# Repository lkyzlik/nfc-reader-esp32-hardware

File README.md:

# NFC Reader ESP32 Hardware
Hardware part of the secure NFC card reader developed on the ESP32 platform. My Bachelor thesis project created at Brno University of Technology.

## Other Parts
* Software part: [github.com/lkyzlik/nfc-reader-esp32-software](https://github.com/lkyzlik/nfc-reader-esp32-software)

## List of Components
| ID         | Component                   | Amount |
|------------|-----------------------------|--------|
| BT1        | LiPol battery 1200mAh       |      1 |
| C1, C3, C6 | Capacitor 100nF THT         |      3 |
| C2, C4     | Capacitor 10μF THT          |      2 |
| C5, C7     | Capacitor 100μF THT         |      2 |
| D1         | Shottky diode THT           |      1 |
| D2         | Red-green LED THT 5mm       |      1 |
| J1         | Barrel Jack                 |      1 |
| J2, J3     | Pin socket 1x15 (for ESP32) |      2 |
| J4         | Pin socket 1x8 (for PN532)  |      1 |
| Q1         | PMOS transistor SMD         |      1 |
| R1         | Resistor 2kΩ THT            |      1 |
| R2,R3      | Resistor 330Ω THT           |      2 |
| R4, R6, R7 | Resistor 4.7kΩ THT          |      3 |
| R5         | Resistor 1kΩ THT            |      1 |
| U1         | MCP73832 IC SMD             |      1 |
| U2         | LF33 IC SMD                 |      1 |
|            | Source DC 5V                |      1 |
|            | PCB with manufacturing      |      1 |
|            | [ESP32 DevKit v1](https://docs.zerynth.com/latest/official/board.zerynth.doit_esp32/docs/index.html)      |      1 |
|            | [PN532 module](https://components101.com/wireless/pn532-nfc-rfid-module)     |      1 |

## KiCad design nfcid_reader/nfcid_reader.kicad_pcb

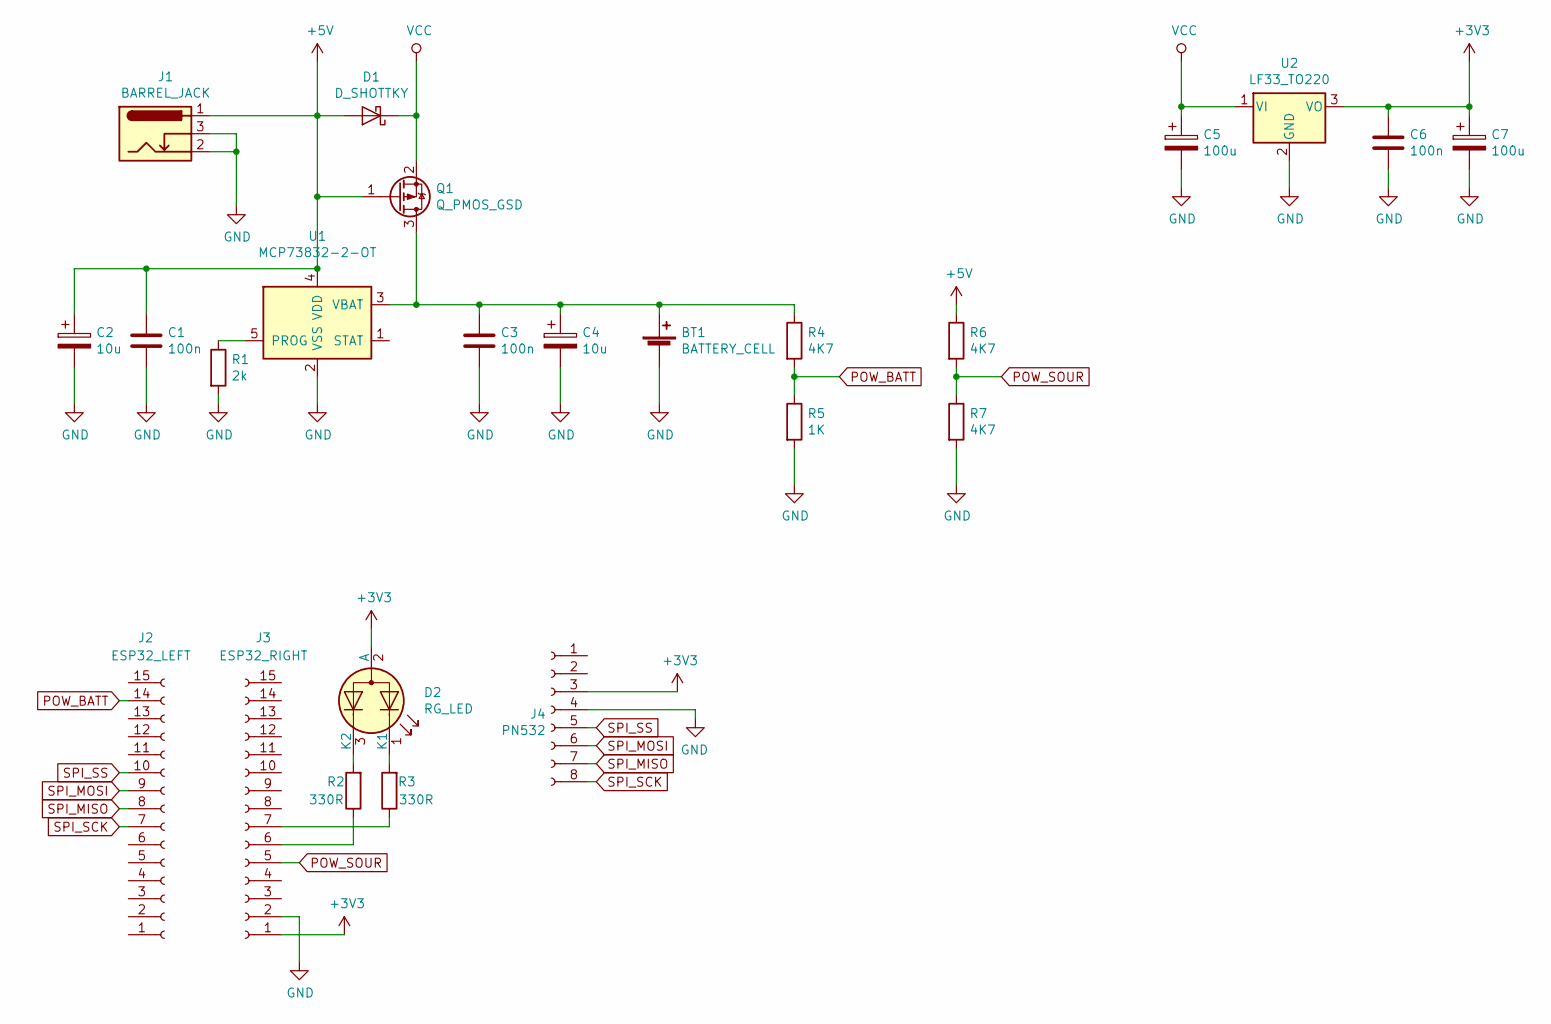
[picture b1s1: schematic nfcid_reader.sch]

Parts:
BT1: BATTERY_CELL; TestPoint_2Pads_Pitch2.54mm_Drill0.8mm
C1, C3, C6: 100n; C_Disc_D3.0mm_W1.6mm_P2.50mm
C2, C4: 10u; CP_Radial_D6.3mm_P2.50mm
C5, C7: 100u; CP_Radial_D6.3mm_P2.50mm
D1: D_SHOTTKY; D_A-405_P7.62mm_Horizontal
D2: RG_LED; LED_D5.0mm-3
J1: BARREL_JACK; BarrelJack_Horizontal
J2: ESP32_LEFT; PinSocket_1x15_P2.54mm_Vertical
J3: ESP32_RIGHT; PinSocket_1x15_P2.54mm_Vertical
J4: PN532; PinSocket_1x08_P2.54mm_Horizontal
Q1: Q_PMOS_GSD; SOT-23_Handsoldering
R1: 2k; R_Axial_DIN0204_L3.6mm_D1.6mm_P7.62mm_Horizontal
R2, R3: 330R; R_Axial_DIN0204_L3.6mm_D1.6mm_P7.62mm_Horizontal
R4, R6, R7: 4K7; R_Axial_DIN0204_L3.6mm_D1.6mm_P7.62mm_Horizontal
R5: 1K; R_Axial_DIN0204_L3.6mm_D1.6mm_P7.62mm_Horizontal
U1: MCP73832-2-OT; SOT-23-5
U2: LF33_TO220; TO-252-2

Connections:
+3V3: C6.1, C7.1, D2.2 (A), J3.1, J4.3, U2.3 (VO)
+5V: C1.1, C2.1, D1.2 (A), J1.1, Q1.1 (G), R6.1, U1.4 (VDD)
GND: BT1.2 (-), C1.2, C2.2, C3.2, C4.2, C5.2, C6.2, C7.2, J1.2, J1.3, J3.2, J4.4, R1.2, R5.2, R7.2, U1.2 (VSS), U2.2 (GND)
unnamed: BT1.1 (+), C3.1, C4.1, Q1.3 (D), R4.1, U1.3 (VBAT)
unnamed: D2.1 (K1), R3.2
unnamed: D2.3 (K2), R2.2
unnamed: J3.6, R2.1
unnamed: J3.7, R3.1
unnamed: R1.1, U1.5 (PROG)
POW_BATT: J2.14, R4.2, R5.1
POW_SOUR: J3.5, R6.2, R7.1
SPI_MISO: J2.8, J4.7
SPI_MOSI: J2.9, J4.6
SPI_SCK: J2.7, J4.8
SPI_SS: J2.10, J4.5
VCC: C5.1, D1.1 (K), Q1.2 (S), U2.1 (VI)

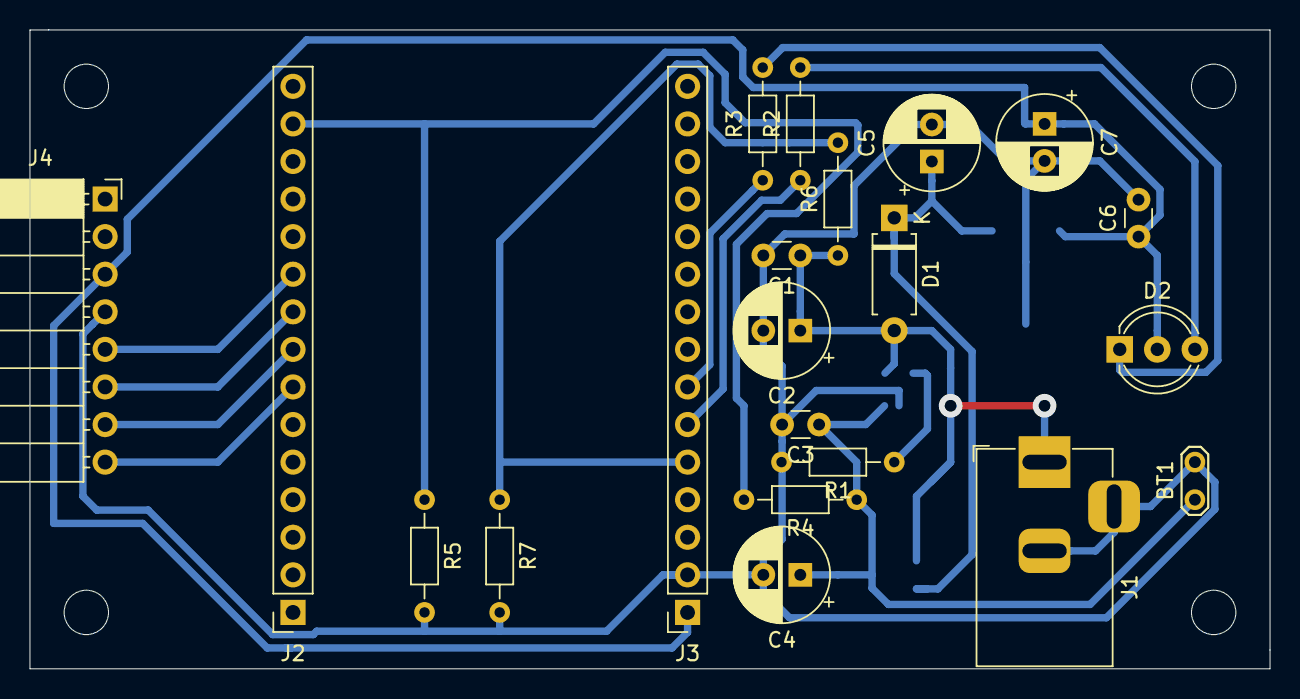
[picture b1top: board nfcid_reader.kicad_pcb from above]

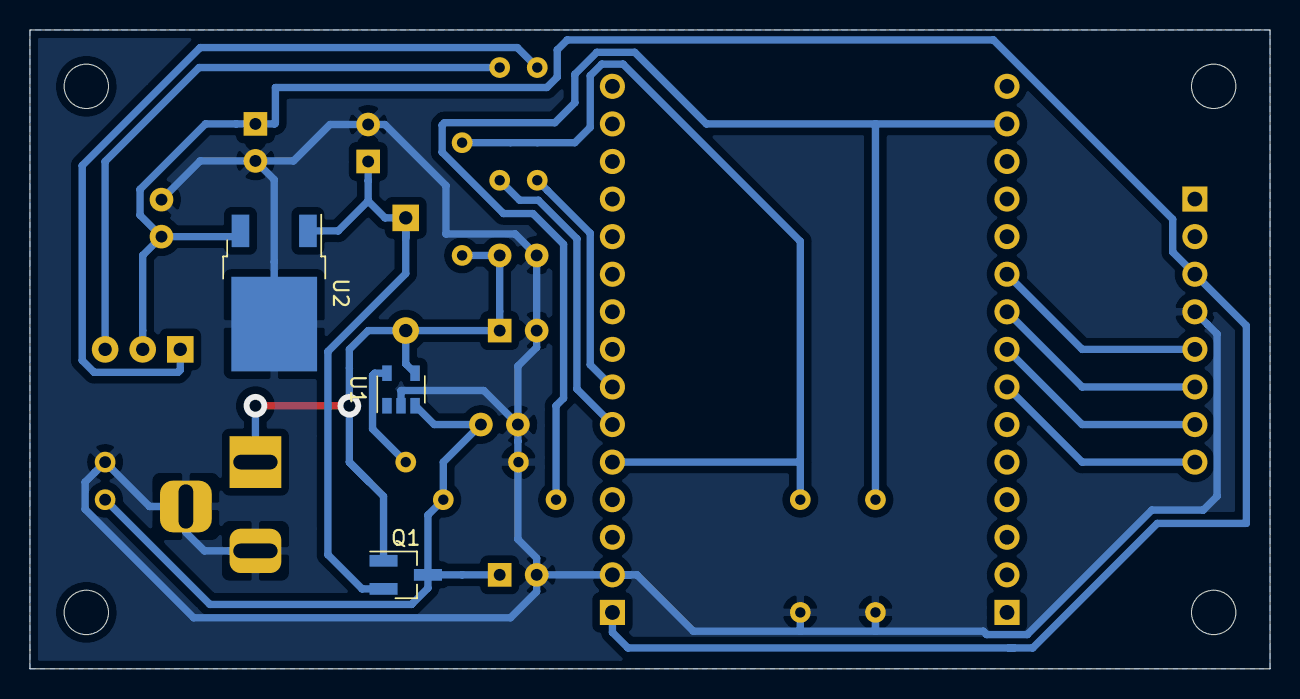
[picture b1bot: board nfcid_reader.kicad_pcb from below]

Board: 2 copper layers, 83.8 x 43.2 mm, 24 parts (3 on the bottom side), 16 nets.

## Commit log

2020-04-12 First commit.
2020-04-14 First draft of the scheme.
2020-04-16 Scheme update. Footprint assignation started.
2020-05-01 First draft. Problems to be solved: thick via, bridge.
2020-05-02 Fixed thick track, ESP orentation. Added bridge, edge cuts.
2020-05-04 Minor fixes.
2020-05-04 RC-1: Added votage dividers. J4 fliped.
2020-05-06 RC-2: U2 changed to SMD. LED moved.
2020-05-07 RC-3: Tracks moved to back. SMDs fliped.
2020-05-22 RC4: Fixed wrong ADC pin connection.
2020-07-22 v1.0: Fixed PN532 polarisation. Updated readme.
2020-07-22 Deleted obsolite files. New folder.
2020-07-22 Updated readme.
2020-07-22 Added license.
